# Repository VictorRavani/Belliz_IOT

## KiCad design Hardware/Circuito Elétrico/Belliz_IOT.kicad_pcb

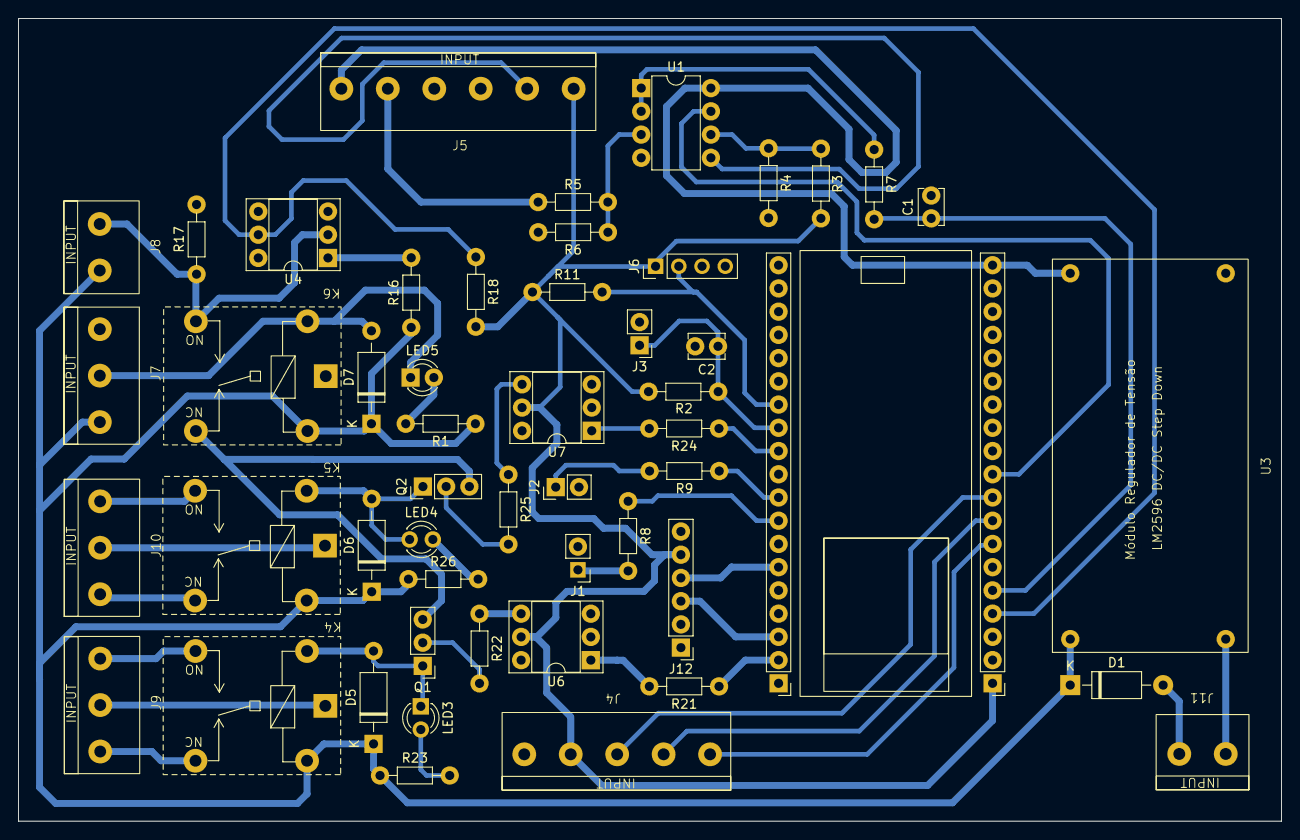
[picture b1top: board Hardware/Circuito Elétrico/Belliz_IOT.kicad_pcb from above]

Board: 2 copper layers, 138.1 x 87.8 mm, 51 parts (0 on the bottom side), 48 nets.

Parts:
C1, C2: 100nF; C_Disc_D3.8mm_W2.6mm_P2.50mm
D1, D5, D6, D7: 1N4007; D_DO-41_SOD81_P10.16mm_Horizontal
J1: Led Vermelho; PinHeader_1x02_P2.54mm_Vertical
J2: Led Verde; PinHeader_1x02_P2.54mm_Vertical
J3: Botão config; PinHeader_1x02_P2.54mm_Vertical
J4: Conn_01x05; KRE_5Vias
J5: Conn_01x06; KRE_6Vias
J6: DHT22; PinHeader_1x04_P2.54mm_Vertical
J7, J9, J10: KRE_3_vias; KRE_3Vias
J8, J11: KRE_2Vias
J12: RTC-DS3231; PinHeader_1x06_P2.54mm_Vertical
K4, K5, K6: AX1RC2; AX1RC
LED3, LED4, LED5: LED_VM; LED_D3.0mm
Q1, Q2: BC547; PinHeader_1x03_P2.54mm_Vertical
R1, R23, R26: 820R; R_Axial_DIN0204_L3.6mm_D1.6mm_P7.62mm_Horizontal
R2, R5, R18: 10K; R_Axial_DIN0204_L3.6mm_D1.6mm_P7.62mm_Horizontal
R3: 750R; R_Axial_DIN0204_L3.6mm_D1.6mm_P7.62mm_Horizontal
R4: 2K2; R_Axial_DIN0204_L3.6mm_D1.6mm_P7.62mm_Horizontal
R6: 20K; R_Axial_DIN0204_L3.6mm_D1.6mm_P7.62mm_Horizontal
R7: 100R; R_Axial_DIN0204_L3.6mm_D1.6mm_P7.62mm_Horizontal
R8, R9, R21, R24: 330R; R_Axial_DIN0204_L3.6mm_D1.6mm_P7.62mm_Horizontal
R11: 4K7; R_Axial_DIN0204_L3.6mm_D1.6mm_P7.62mm_Horizontal
R16: 3K3; R_Axial_DIN0204_L3.6mm_D1.6mm_P7.62mm_Horizontal
R17: 220K; R_Axial_DIN0204_L3.6mm_D1.6mm_P7.62mm_Horizontal
R22, R25: 1K; R_Axial_DIN0204_L3.6mm_D1.6mm_P7.62mm_Horizontal
U1: LM358; DIP-8_W7.62mm
U3: Módulo_DC-DC_2576
U4, U6, U7: CNY17-1; DIP-6_W7.62mm_Socket
U5: ESP32_DevKit

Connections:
+3.3V: J4.4, J5.6, J6.1, J12.5, R2.1, R3.1, R11.1, R18.2, U5.1 (3V3), U6.5, U7.5
+5V: J5.1, U1.8 (V+), U3.3 (OUT+), U5.19 (5V)
+12V: D1.1 (K), D5.1 (K), D6.1 (K), D7.1 (K), J7.1, J8.1, K4.5, K5.5, K6.5, R1.1, R16.1, R23.1, R26.1, U3.1 (IN+)
/Microcontroller/ACS712_BUF: C1.1, R7.2, U5.5 (GPIO34/ADC6)
/Microcontroller/ACS712_OUT: J5.2, R5.1
/Microcontroller/BT_CONFIG: C2.1, J3.1, R2.2, U5.27 (GPIO16/RX2)
/Microcontroller/DHT22: J6.2, R11.2, U5.26 (GPIO4/ADC10)
/Microcontroller/FIRE_GPIO: R18.1, U4.5, U5.4 (GPIO39/ADC3)
/Microcontroller/LED_VD: R9.1, U5.30 (GPIO18/SCK)
/Microcontroller/LED_VM: R8.1, U5.31 (GPIO19/MISO)
/Microcontroller/MAX6675_CS: J4.2, U5.8 (GPIO33/ADC5)
/Microcontroller/MAX6675_SCK: J4.3, U5.9 (GPIO25/ADC18)
/Microcontroller/MAX6675_SO: J4.1, U5.7 (GPIO32/ADC4)
/Microcontroller/OUT_RPM: U1.7, U5.10 (GPIO26/ADC19)
/Microcontroller/RELE_1: R21.1, U5.37 (GPIO23/MOSI)
/Microcontroller/RELE_2: R24.1, U5.28 (GPIO17/TX2)
/Microcontroller/SCL: J12.3, U5.36 (GPIO22/SCL)
/Microcontroller/SDA: J12.4, U5.33 (GPIO21/SDA)
/Microcontroller/TCRT5000: J5.5, U1.5 (+)
/Reles/COM_1: J9.2, K4.2
/Reles/COM_2: J10.2, K5.2
/Reles/GND2: K6.4, Q1.3 (E), Q2.3 (E)
/Reles/OUT_DETECTOR: D7.2 (A), J7.2, K6.1, LED5.1 (K)
/Reles/RELE_1_NA: J9.3, K4.3
/Reles/RELE_1_NF: J9.1, K4.4
/Reles/RELE_2_NA: J10.3, K5.3
/Reles/RELE_2_NF: J10.1, K5.4
/Reles/RELE_3_NA: J8.2, K6.3, R17.1, U4.2
Earth: C1.2, C2.2, J1.2, J2.2, J3.2, J4.5, J5.3, J5.4, J6.4, J7.3, J12.6, K6.2, R4.2, R6.2, R17.2, U1.4 (V-), U3.4 (OUT-), U4.4, U5.14 (GND), U5.32 (GND), U5.38 (GND), U6.2, U7.2
unnamed: D1.2 (A), J11.2
unnamed: D5.2 (A), K4.1, LED3.1 (K), Q1.1 (C)
unnamed: D6.2 (A), K5.1, LED4.1 (K), Q2.1 (C)
unnamed: J1.1, R8.2
unnamed: J2.1, R9.2
unnamed: LED3.2 (A), R23.2
unnamed: LED4.2 (A), R26.2
unnamed: LED5.2 (A), R1.2
unnamed: Q1.2 (B), R22.2
unnamed: Q2.2 (B), R25.2
unnamed: R16.2, U4.1
unnamed: R21.2, U6.1
unnamed: R22.1, U6.4
unnamed: R24.2, U7.1
unnamed: R25.1, U7.4
unnamed: R5.2, R6.1, U1.3 (+)
unnamed: R7.1, U1.1, U1.2 (-)
unnamed: R3.2, R4.1, U1.6 (-)
unnamed: J11.1, U3.2 (IN_-)

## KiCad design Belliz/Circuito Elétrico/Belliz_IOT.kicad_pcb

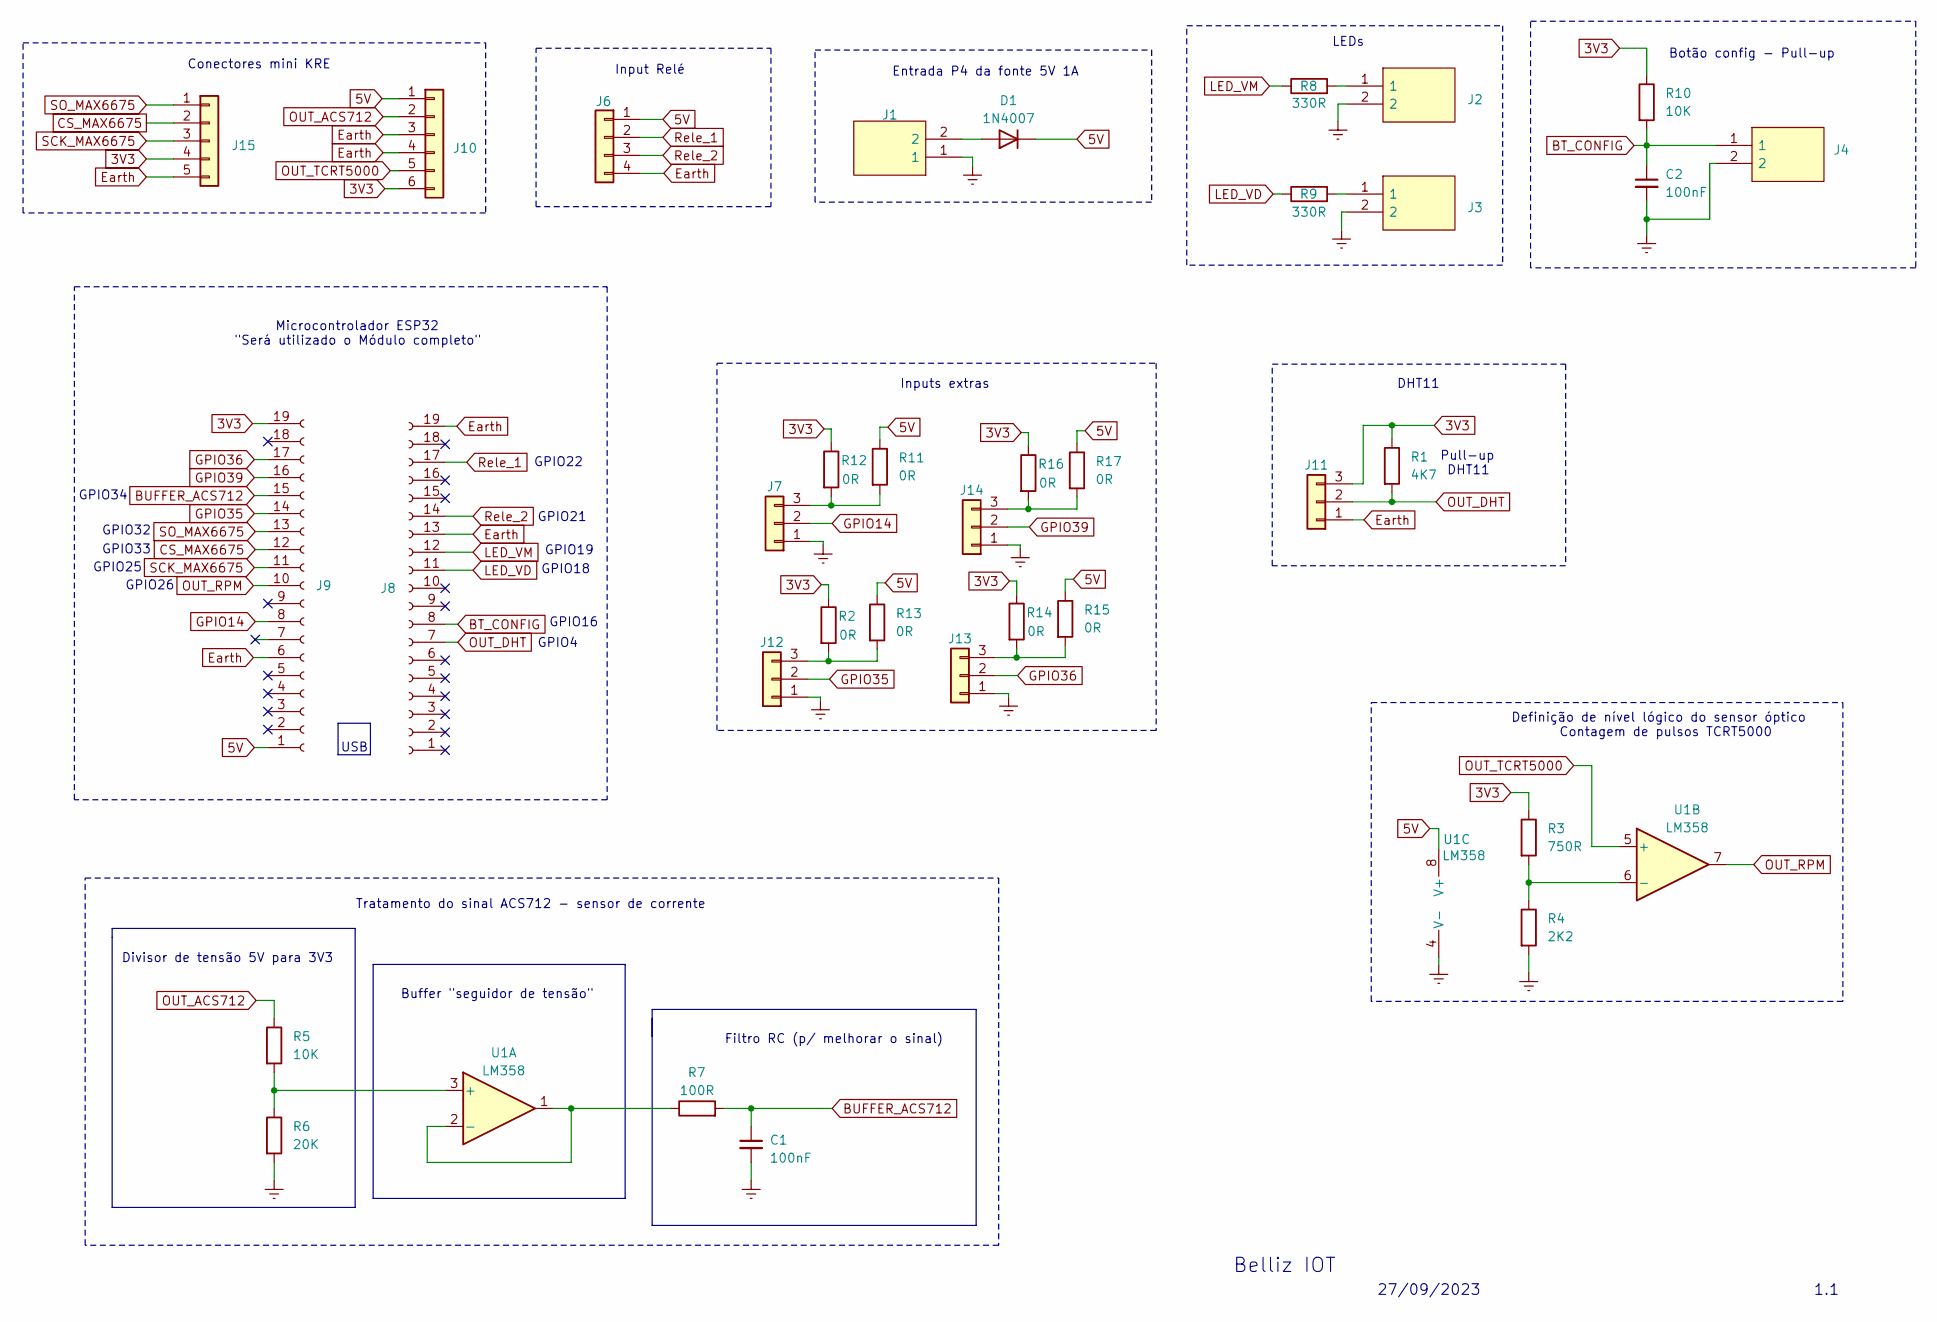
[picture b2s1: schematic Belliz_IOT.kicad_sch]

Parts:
C1, C2: 100nF; C_0805_2012Metric
D1: 1N4007; D_DO-41_SOD81_P10.16mm_Horizontal
J1: KK_2vias; Mouser Part Number 571-440054-2
J2, J3, J4: 440054-2; KK_2vias; Mouser Part Number 571-440054-2
J6: Conn_01x04; KK_4vias
J7, J11, J12, J13, J14: Conn_01x03; KK_3Vias
J8, J9: Conn_01x19_Socket; Pin_header_19vias_female
J10: Conn_01x06; KRE_6Vias
J15: Conn_01x05; KRE_5Vias
R1: 4K7; R_0805_2012Metric
R2, R11, R12, R13, R14, R15, R16, R17: 0R; R_0805_2012Metric
R3: 750R; R_0805_2012Metric
R4: 2K2; R_0805_2012Metric
R5, R10: 10K; R_0805_2012Metric
R6: 20K; R_0805_2012Metric
R7: 100R; R_0805_2012Metric
R8, R9: 330R; R_0805_2012Metric
U1: LM358; DIP-8_W7.62mm

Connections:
3V3: J9.19, J10.6, J11.3, J15.4, R1.1, R2.1, R3.1, R10.1, R12.1, R14.1, R16.1
5V: D1.1 (K), J6.1, J9.1, J10.1, R11.1, R13.1, R15.1, R17.1, U1.8 (V+)
BT_CONFIG: C2.1, J4.1, J8.8, R10.2
BUFFER_ACS712: C1.1, J9.15, R7.2
CS_MAX6675: J9.12, J15.2
Earth: C1.2, C2.2, J1.1, J2.2, J3.2, J4.2, J6.4, J7.1, J8.13, J8.19, J9.6, J10.3, J10.4, J11.1, J12.1, J13.1, J14.1, J15.5, R4.2, R6.2, U1.4 (V-)
GPIO14: J7.2, J9.8
GPIO35: J9.14, J12.2
GPIO36: J9.17, J13.2
GPIO39: J9.16, J14.2
LED_VD: J8.11, R9.1
LED_VM: J8.12, R8.1
unnamed: D1.2 (A), J1.2
unnamed: J2.1, R8.2
unnamed: J3.1, R9.2
unnamed: J7.3, R11.2, R12.2
unnamed: J12.3, R2.2, R13.2
unnamed: J13.3, R14.2, R15.2
unnamed: J14.3, R16.2, R17.2
unnamed: R5.2, R6.1, U1.3 (+)
unnamed: R7.1, U1.1, U1.2 (-)
unnamed: R3.2, R4.1, U1.6 (-)
OUT_ACS712: J10.2, R5.1
OUT_DHT: J8.7, J11.2, R1.2
OUT_RPM: J9.10, U1.7
OUT_TCRT5000: J10.5, U1.5 (+)
Rele_1: J6.2, J8.17
Rele_2: J6.3, J8.14
SCK_MAX6675: J9.11, J15.3
SO_MAX6675: J9.13, J15.1

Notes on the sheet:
GPIO4
Entrada P4 da fonte 5V 1A
Microcontrolador ESP32 "Será utilizado o Módulo completo"
GPIO18
GPIO33
LEDs
GPIO22
Filtro RC (p/ melhorar o sinal)
Inputs extras
Belliz IOT
Pull-up DHT11
Tratamento do sinal ACS712 - sensor de corrente
GPIO34
Buffer "seguidor de tensão"
USB
Input Relé
27/09/2023
Conectores mini KRE
GPIO21
Botão config - Pull-up
Definição de nível lógico do sensor óptico Contagem de pulsos TCRT5000
GPIO19
GPIO16
GPIO32
GPIO25
DHT11
1.1
GPIO26
Divisor de tensão 5V para 3V3

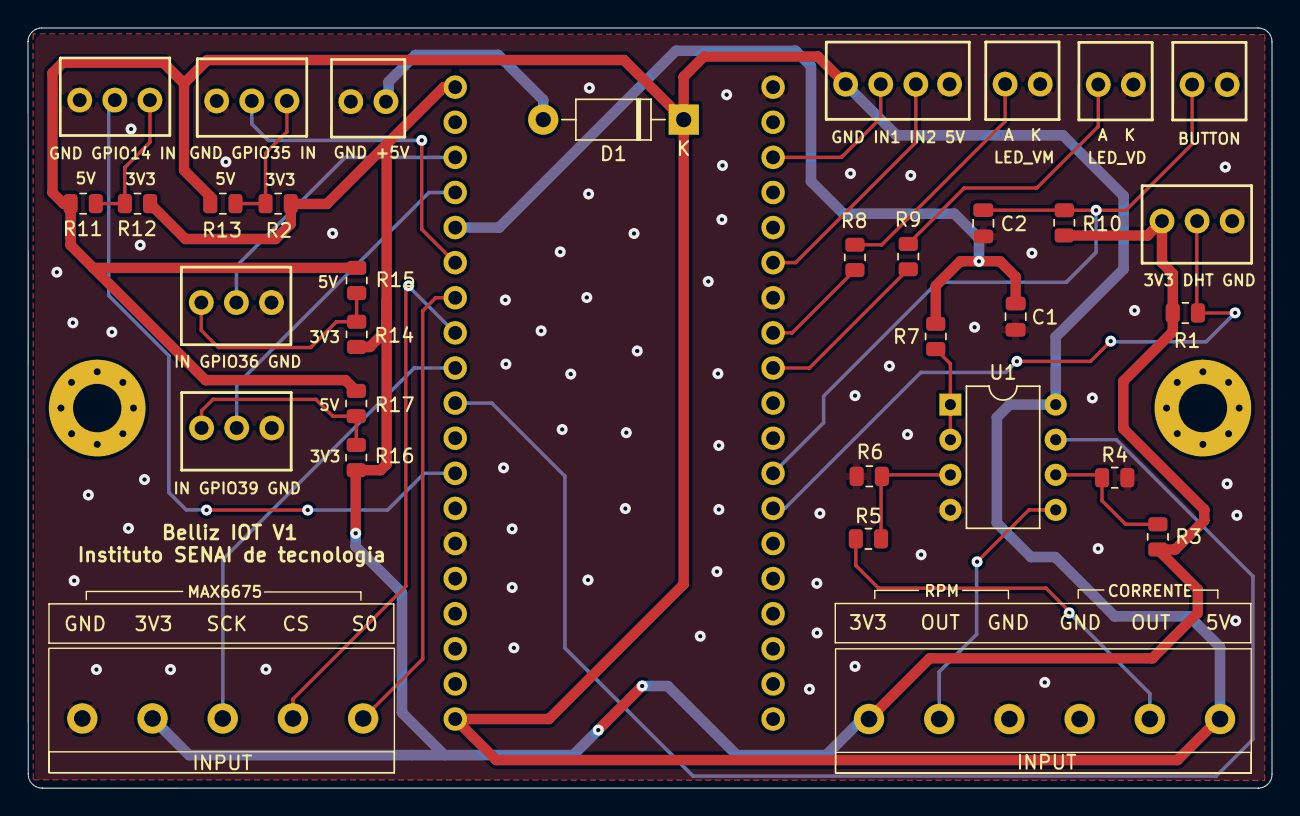
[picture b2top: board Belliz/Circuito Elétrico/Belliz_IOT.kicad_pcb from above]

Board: 2 copper layers, 90.0 x 55.0 mm, 35 parts (0 on the bottom side), 30 nets.

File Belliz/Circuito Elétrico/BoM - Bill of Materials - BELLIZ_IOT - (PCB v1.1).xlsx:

Bill of Materials
Company Name: |  |  |  | Instituto SENAI de tecnologia em eletrônica e automação
 |  |  | Address | R. Jaguaré Mirim, 71 - Vila Leopoldina, São Paulo - SP, 05311-020 - Setor: IST 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
 |  |  | Authorized persons | Victor Ravani; Gustavo Oliveira; Igor Messias; Fabio Rizzo
Project Name: |  |  |  | Belliz IOT – (PCB 1.1)
RESISTORS
ID | Qty. | Qty. * 4 | Part Designator | Manufacturer Number | Description
1 | 1 | 4 | R1 | Resistor SMD 4K7 0805 0,125W (1/8W) 5% | Resistor SMD 0805 4K7
2 | 8 | 32 | R2, R11, R12, R13, R14, R15, R16, R17 (All DNP) | Resistor SMD 0R 0805 | Resistor SMD 0805 0R
3 | 1 | 4 | R3 | Resistor SMD 750R 0805 | Resistor SMD 0805 750R
4 | 1 | 4 | R4 | Resistor SMD 2K2 0805 0,125W (1/8W) 5% | Resistor SMD 0805 2K2
5 | 2 | 8 | R5, R10 | Resistor SMD 10K 0805 0,125W (1/8W) 5% | Resistor SMD 0805 10K
6 | 1 | 4 | R6 | Resistor SMD 20K 0805 | Resistor SMD 0805 20K
7 | 1 | 4 | R7 | Resistor SMD 100R 0805 | Resistor SMD 0805 100R
8 | 2 | 8 | R8, R9 | Resistor SMD 330R 0805 0,125W (1/8W) 5% | Resistor SMD 0805 330R
CAPACITORS
ID | Qty. | Qty. | Part Designator | Manufacturer Number | Description
1 | 2 |  | C1, C2 | Capacitor Cerâmico Smd 100nf 0805 50v X7r | Capacitor cerâmico SMD 0805 100nF
INTREGRATED CIRCUITS
ID | Qty. | Qty. | Part Designator | Manufacturer Number | Description
1 | 1 | 4 | U1 | LM358 | Integrated Circuit
SYSTEM ON MODULE
ID | Qty. | Qty. | Part Designator | Manufacturer Number | Description
1 | 1 | 4 | IC1 | ESP32 | Microcontroller
CONNECTORS
ID | Qty. | Qty. | Part Designator | Manufacturer Number | Description
1 | 4 |  | J1, J2, J3, J4 | Conector KK 2 vias | Conector
2 | 1 |  | J6 | Conector KK 4 vias | Conector
3 | 5 |  | J7(DNP), J11, J12(DNP), J13(DNP), J14(DNP) | Conector KK 3 vias | Conector
4 | 1 |  | J10, | Conector KRE 6 vias | Conector
5 | 1 |  | J15 | Conector KRE 5 vias | Conector
6 | 2 |  | J8, J9 | Pin header female 19 vias | Conector

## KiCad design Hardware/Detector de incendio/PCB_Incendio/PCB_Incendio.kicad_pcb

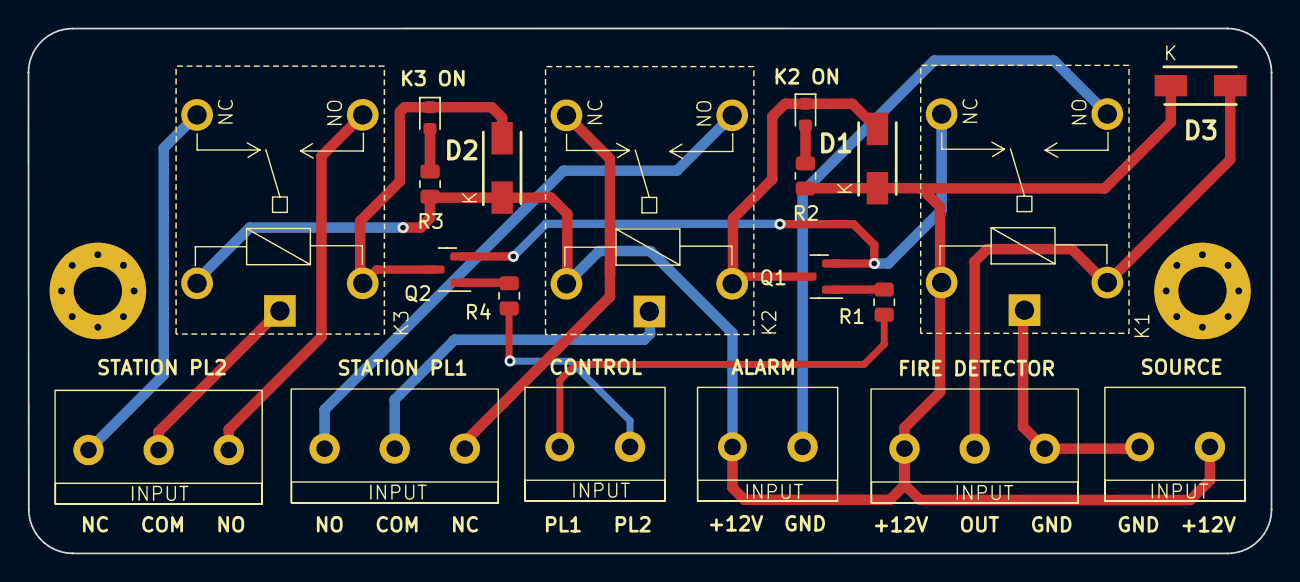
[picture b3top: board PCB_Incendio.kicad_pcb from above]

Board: 2 copper layers, 90.0 x 38.0 mm, 21 parts (1 on the bottom side), 19 nets.

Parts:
D1, D2, D3: 1N4007; Diodo_SM_DO-214
J1, J2, J6: KRE_2Vias
J3, J4, J5: KRE_3_vias; KRE_3Vias
K1, K2, K3: AX1RC2; AX1RC
LED1, LED2: LED_VM; LED_0603_1608Metric
Q1, Q2: BC817; SOT-23
R1, R4: 2K2; R_0805_2012Metric
R2, R3: 820R; R_0805_2012Metric
Ref**: Val**; Logo_SENAI_PCB_V3

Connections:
12V: D1.1 (K), D2.1 (K), D3.1 (K), J1.1, J2.2, J5.3, K1.5, K2.5, K3.5, R2.1, R3.1
unnamed: D1.2 (A), K2.1, LED1.1 (K), Q1.3 (C)
unnamed: D2.2 (A), K3.1, LED2.1 (K), Q2.3 (C)
unnamed: D3.2 (A), J5.2, K1.1
unnamed: J1.2, J5.1, K1.2
unnamed: J2.1, K1.3
unnamed: J3.1, K2.4
unnamed: J3.2, K2.2
unnamed: J3.3, K2.3
unnamed: J4.1, K3.3
unnamed: J4.2, K3.2
unnamed: J4.3, K3.4
unnamed: LED1.2 (A), R2.2
unnamed: LED2.2 (A), R3.2
unnamed: Q1.1 (B), R1.2
unnamed: K1.4, Q1.2 (E), Q2.2 (E)
unnamed: Q2.1 (B), R4.2
PL1: J6.2, R1.1
PL2: J6.1, R4.1

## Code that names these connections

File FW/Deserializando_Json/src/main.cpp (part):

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////////////////////////////// MAPEAMENTO DE HARWARE //////////////////////////////////

#define PULSE 26
#define SCK_MAX6675 25
#define CS_MAX6675 33
#define SO_MAX6675 32
#define RELE_1 23 // Led RELE_1 = 23
#define RELE_2 17 // Led RELE_1 = 17
#define DHTPIN 4 //PINO DIGITAL UTILIZADO PELO DHT22
#define GPIO_BUTTON 16
#define GPIO_LED_VM 19 // Led VM =19
#define GPIO_LED_VD 18 // Led VD =18
#define DETECTOR_FIRE 39

 // GPIO 34 = ADC1_CHANNEL_6 (BUFFER_ACS712)

////////////////////////////// DEFINIÇÕES //////////////////////////////////////////////

#define DHTTYPE DHT22 //define o modelo do sensor (DHT22 / AM2302)
#define MAX 600
#define BAUD_RATE_SERIAL 115200
#define TIMER_NUM 0
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
void setup() {

  pinMode(RELE_1, OUTPUT);
  pinMode(RELE_2, OUTPUT);
  pinMode(GPIO_LED_VM, OUTPUT);
  pinMode(GPIO_LED_VD, OUTPUT);
  pinMode(DETECTOR_FIRE, INPUT);

  digitalWrite(GPIO_LED_VM, LOW);
  digitalWrite(GPIO_LED_VD, LOW);

  Serial.begin(BAUD_RATE_SERIAL);

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  else {
    if (debug == true){
      Serial.println("Broker: Fail in conection! ");
      digitalWrite(GPIO_LED_VD, LOW);
      Serial.print("Broker state: ");
      Serial.println(client.state());
      
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
    if (debug == true){
      Serial.println("Broker: CONNECTED!");
      digitalWrite(GPIO_LED_VD, HIGH);

      if(CurrentState != fire_detector){
        CurrentState = send_data;
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    }
  }
  else {
    digitalWrite(GPIO_LED_VD, HIGH);
    brokerConnect();
    if (!client.state()){
      if(CurrentState != fire_detector){
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
    last_version_fw = version_fw_float;

    digitalWrite(GPIO_LED_VM, HIGH);

    EEPROM.writeFloat(address_version_fw, last_version_fw);
    EEPROM.commit();
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
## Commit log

2023-05-12 Priemiro commit
2023-05-18 Atualização do circuito eletrico
2023-05-18 Atualização do circuito eletrico 2
2024-01-03 Inclusao da pasta do fw
2024-01-03 Atualizacao de fw, organização e padronização
2024-01-05 código funcional
2024-01-10 Update OTA and subscribe in topic mqtt
2024-01-12 Sensor de incêncio e leds
2024-01-15 Melhorar retomada do Fire e Buton On Off
2024-01-16 finalização parcial - Pronto para testes
2024-01-18 Atualização detector de incêndio
2024-04-18 atualização de arquivos
2024-05-17 Atualização da última versão de firmware
2024-06-17 Atualização do firmware
